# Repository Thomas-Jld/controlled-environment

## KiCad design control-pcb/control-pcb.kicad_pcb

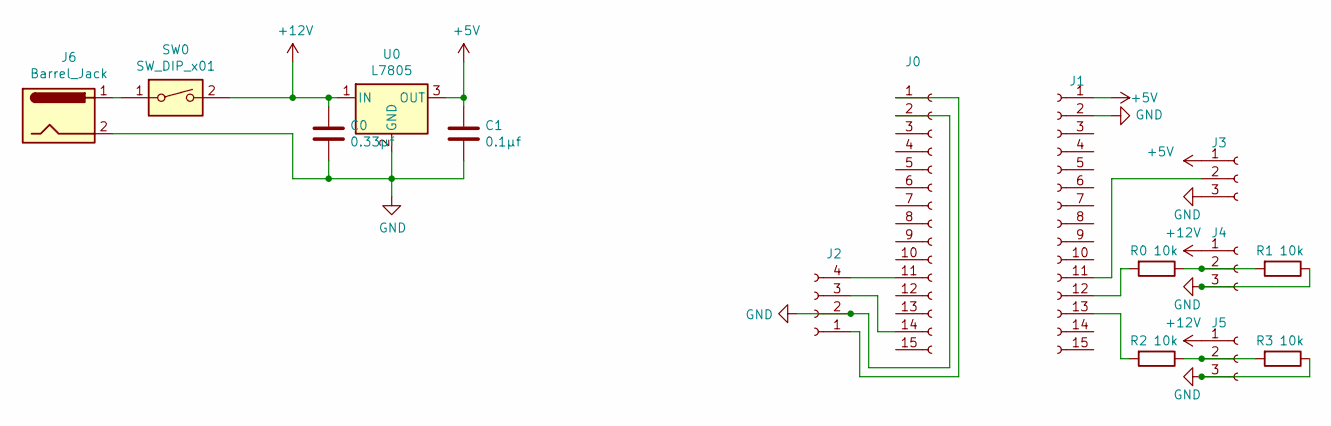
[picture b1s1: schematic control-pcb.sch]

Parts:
C0: 0.33µf; C_0603_1608Metric
C1: 0.1µf; C_0603_1608Metric
J0, J1: Conn_01x15_Female; PinHeader_1x15_P2.54mm_Vertical
J2: Conn_01x04_Female; PinHeader_1x04_P2.54mm_Vertical
J3, J4, J5: Conn_01x03_Female; PinHeader_1x03_P2.54mm_Vertical
J6: Barrel_Jack; BarrelJack_Horizontal
R0, R1, R2, R3: 10k; R_1206_3216Metric
SW0: SW_DIP_x01; SW_DPDT_CK_JS202011JCQN
U0: L7805; PinHeader_1x03_P2.54mm_Vertical

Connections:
+5V: C1.1, J1.1, J3.1, U0.3 (OUT)
+12V: C0.1, J4.1, J5.1, SW0.2, U0.1 (IN)
GND: C0.2, C1.2, J0.2, J1.2, J2.2, J3.3, J4.3, J5.3, J6.2, R1.1, R3.1, U0.2 (GND)
unnamed: J0.1, J2.1
unnamed: J0.11, J2.4
unnamed: J0.14, J2.3
unnamed: J1.11, J3.2
unnamed: J1.12, R0.2
unnamed: J1.13, R2.2
unnamed: J4.2, R0.1, R1.2
unnamed: J5.2, R2.1, R3.2
unnamed: J6.1, SW0.1

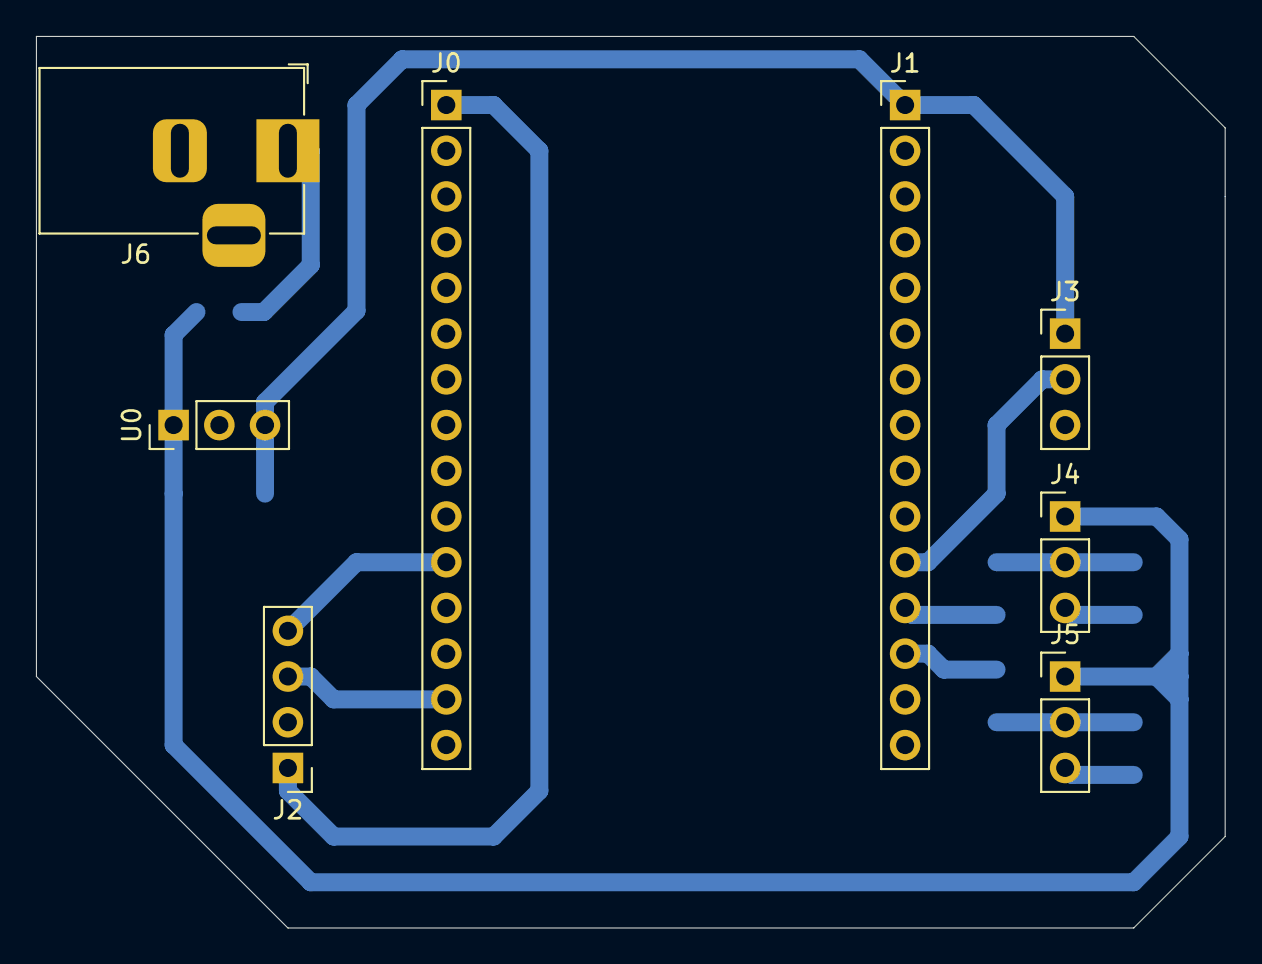
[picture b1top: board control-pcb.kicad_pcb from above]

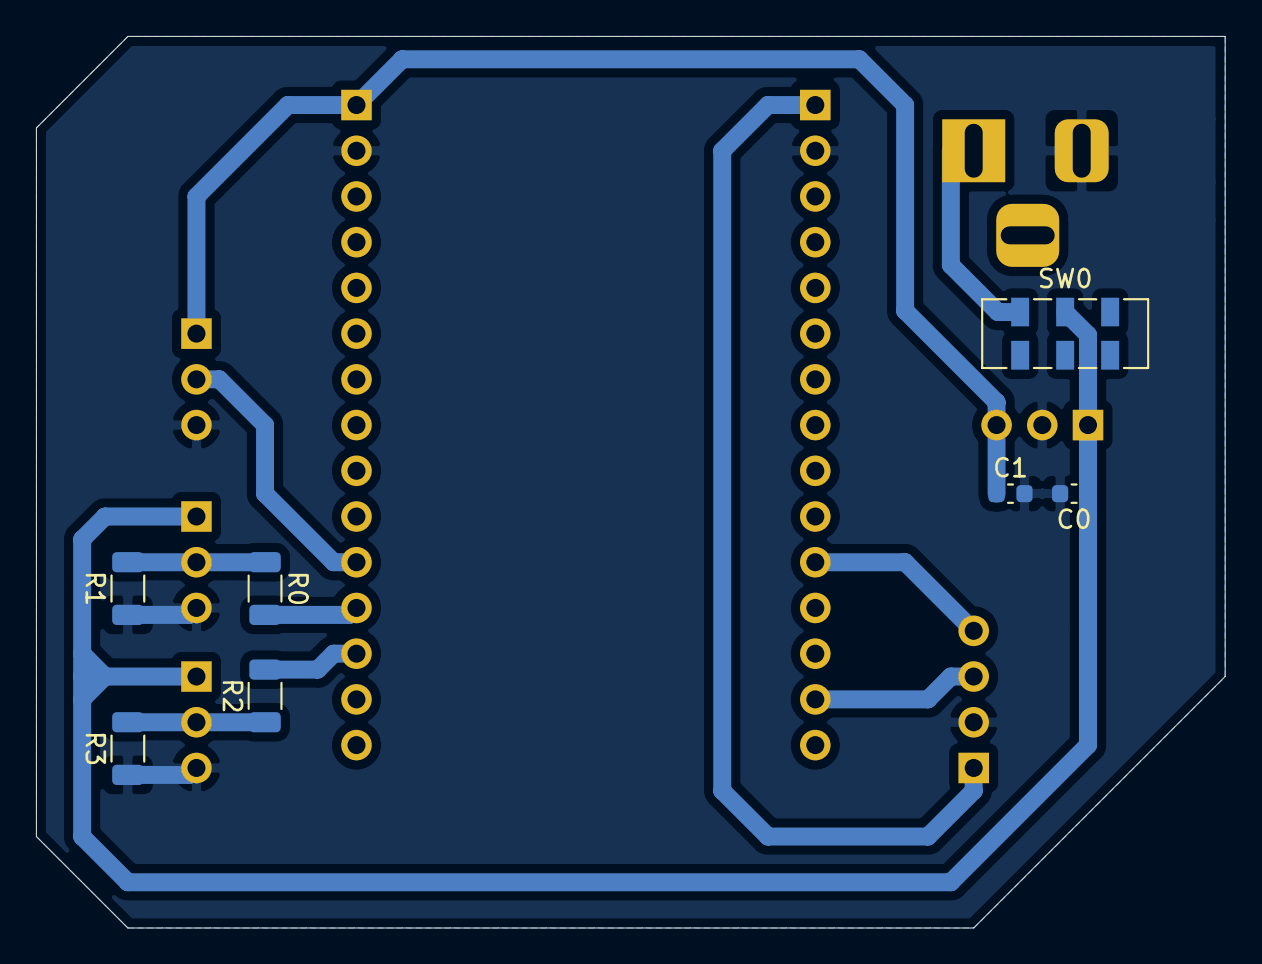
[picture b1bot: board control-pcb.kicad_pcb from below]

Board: 2 copper layers, 66.0 x 49.5 mm, 15 parts (7 on the bottom side), 12 nets.

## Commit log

2021-06-21 Init
2021-06-21 Live plot
2021-06-22 Graph and sensors
2021-07-05 Web based
2021-07-08 PlatformIo Project
2021-07-08 Flask server
2021-07-09 RL graphs
2021-07-16 Creating pcb
2021-07-16 Updated pcb
